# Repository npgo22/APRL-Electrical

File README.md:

# APRL KiCad Projects

APRL KiCad Projects.

## Setup
First, clone the repository with `git clone`. GitHub has a button which gives you the command to do this.
Then, you will have to use `git lfs pull` to get all the 3D models and images.

The projects here rely on `APRL_LIBS` and `KICAD_USER_TEMPLATE_DIR` being set. You can do this by:

1. Going to Preferences > Configure Paths...
2. Setting `APRL_LIBS` to wherever you cloned this repo + `/kicadlibs`.
3. Setting `KICAD_USER_TEMPLATE_DIR` to whatever you set in (2) + `/templates`

## New ALI (Current Project for FQ2026)

### Design
The exigence of this endeavour is twofold:
1. To test the analog frontend designs of our proposed boards for DPF
2. To replace the confusing and elaborate ALI electronics with something that is far better documented and easier to use

The ALI itself can continue to be used for years to come and this reworking of the electronics will not impact it at all. This is going to be its own separate electrical box altogether. The ALI has the following additional limitations, too:
1. Limited I/O
2. Bonded grounds between +24/12/5V power supplies
3. Unknown board-level design decisions/trade-offs made in off-the-shelf components leading to strange artifacts in various measurements
4. Is generally really difficult to understand
5. Mixes bodge-wired custom electronics, off-the-shelf parts, and protoboards
6. Generally has fairly poor mounting
7. Makes use of fairly terrible connectors which are partially damaged and/or have shields which are not properly tied to case GND
8. Is completely full, thus making it impossible to add more electronics
9. Has no methods of cooling, sans the empty hold in the side of the box which completely negate the weather rating of the box itself
10. Uses heterogenous embedded computing ecosystems, requiring cross-domain knowledge of embassy, STM32Cube, and Arduino while doing every single one of them somewhat wrong in one way or another
11. Lacks feedback in many places (error logging namely)
12. Is generally just really hard to work with

Therefore, we have started work on a true replacement. Each of the modules serve a specific task, and are hooked to a common ethernet-based network which is far more performant than the original layout while simultaneously being easier to understand and expand. If you want more I/O, you can just simply add another board within a few minutes. Likewise, by opting for cutouts in the enclosure over dedicated port holes, it is also far easier to revise significant parts of the design without needing to drill through steel. 

#### Power
This system is +5V and +24V only, with +3.3V regulated on each board.

### CANBUS vs Ethernet
On the ground station, we are planning to use Ethernet instead of CANBUS. While this means our session protocol will not be tested in a real-world hotfire scenario, it does mean we can fully exploit each of the features offered by ethernet:
- Higher bandwidth (upwards of ~50x) means we don't have to throttle anything including error logging
- Natural isolation means we don't need any special tricks to get grounded thermocouples to work
- Is just generally far more pleasant to work with
- Does not limit future design decisions should we decide to reuse anything

Each of the modules will have a CAN transceiver anyway available for testing.

## Repository layout

```
kicadlibs/                                 Shared KiCad libraries, referenced as ${APRL_LIBS}
  aprl/                                      APRL's custom symbols and footprints
  aprl/*-noct.pretty                         "aprl/" but without courtyards
  vendor/                                    Third-party libs
  kicad/                                     Vendored stock KiCad libraries
  models/                                    3D models
  APRL_*_Sheet.kicad_wks                     Drawing sheets
  jlcpcb-4layer.kicad_dru                    Canonical JLCPCB design rules
.github/scripts                              Helper scripts runnable via Just and GH actions

ali/v2/                                    New ALI electronics
ali/v1/                                    Old ALI electronics
ophio/                                     DPF Vehicle Boards
misc/                                      Other endeavours
```

## What's not in this repo
- Old code (incl thermocouple 1A's CubeMX and Embassy variants)
- Prototypes (pending ordering)
- ALI ADC hardware (pending import)

## AI Usage
You may use AI to research topics and to write one-off scripts which do minor modifications and automate tedious, minor tasks. For example, if you need to color in a bunch of models feel free to.

What you *cannot* use it for is end to end electrical design, layout, and documentation. Documents should be written by people, and a schematic falls under this category. Likewise, using AI to automate layout is A. ineffective because it does not generate high-quality layouts and B. defeats the purpose of this club, which is to learn about electronics.

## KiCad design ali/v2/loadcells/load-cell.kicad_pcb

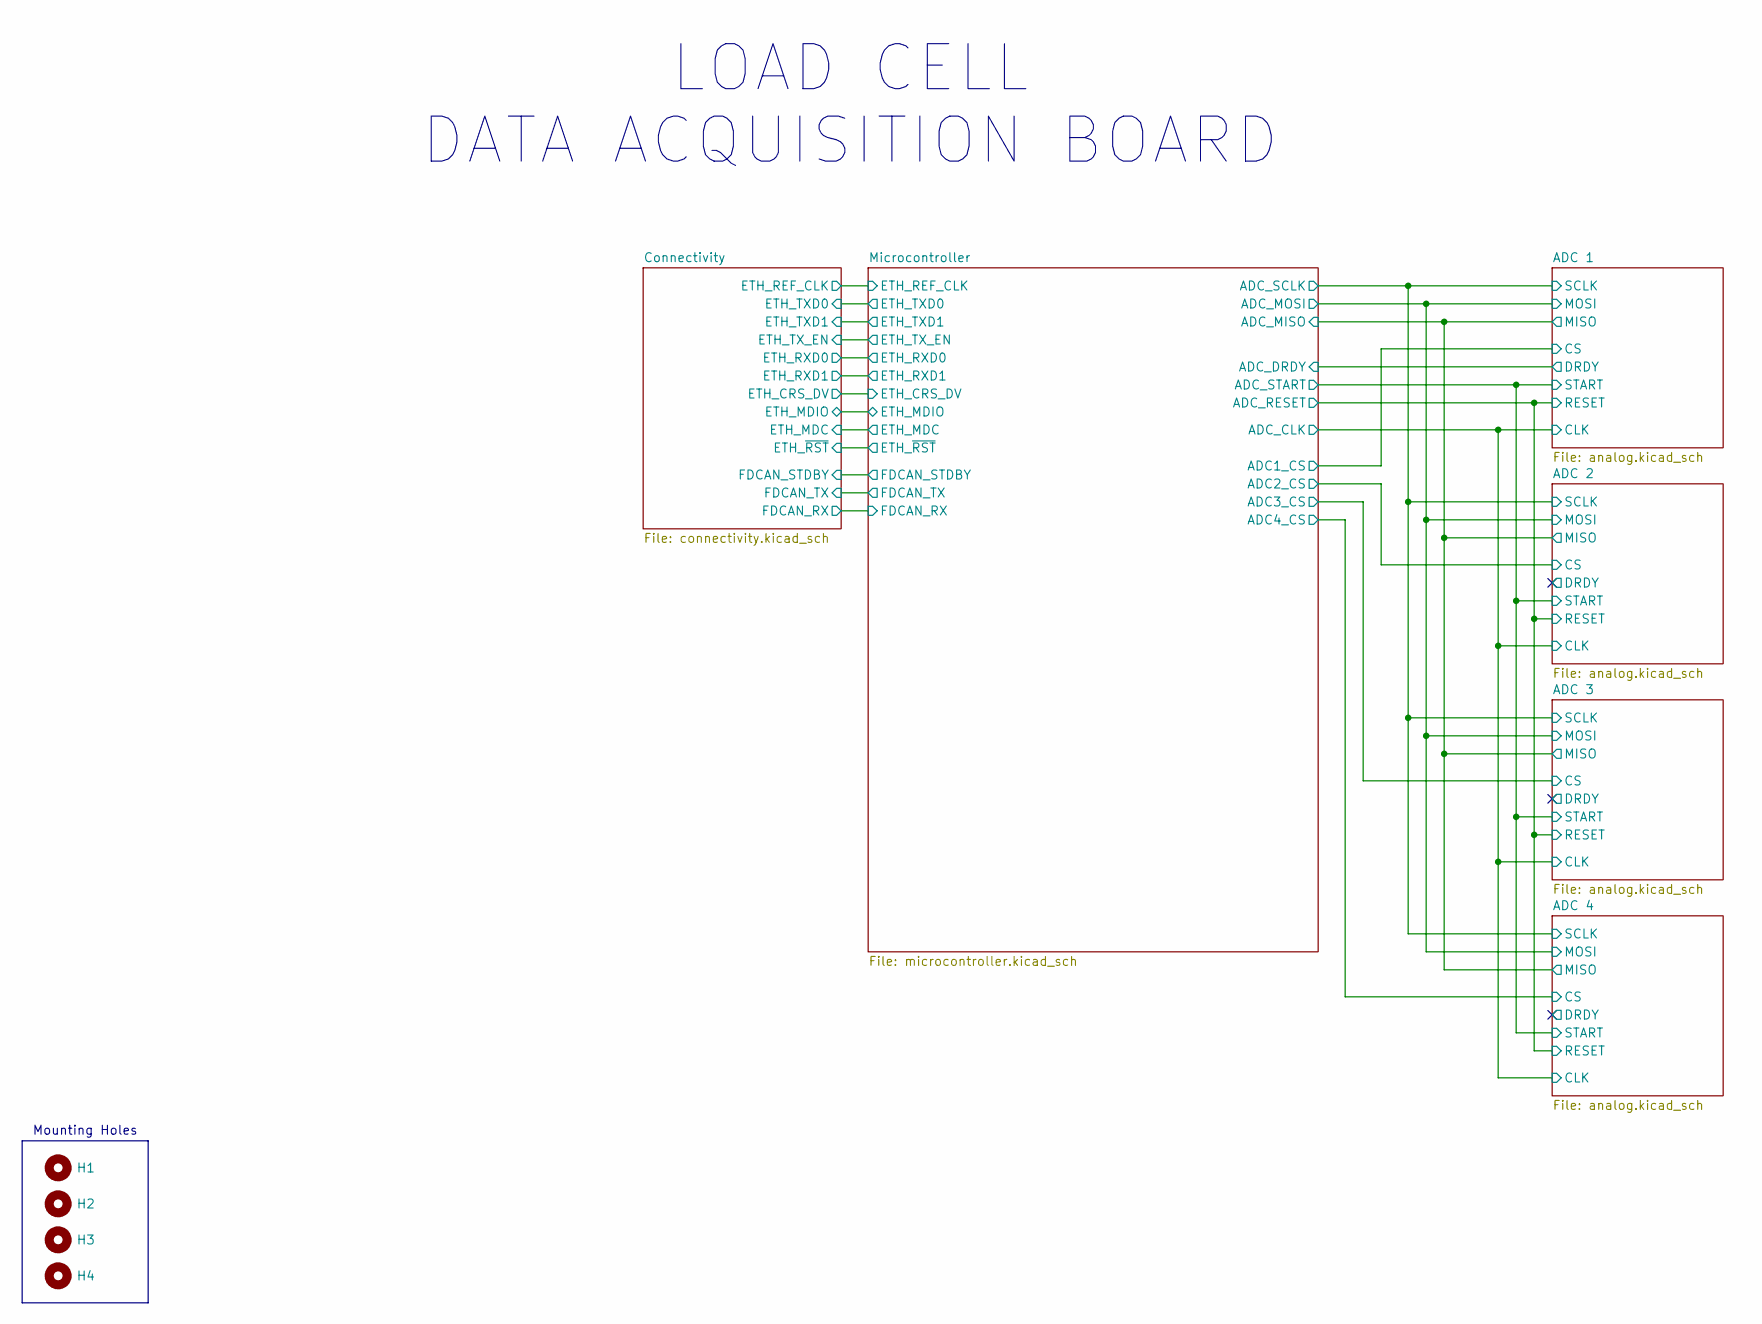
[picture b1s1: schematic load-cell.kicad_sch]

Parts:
H1, H2, H3, H4: MountingHole; MountingHole_3.2mm_M3

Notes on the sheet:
LOAD CELL DATA ACQUISITION BOARD
Mounting Holes

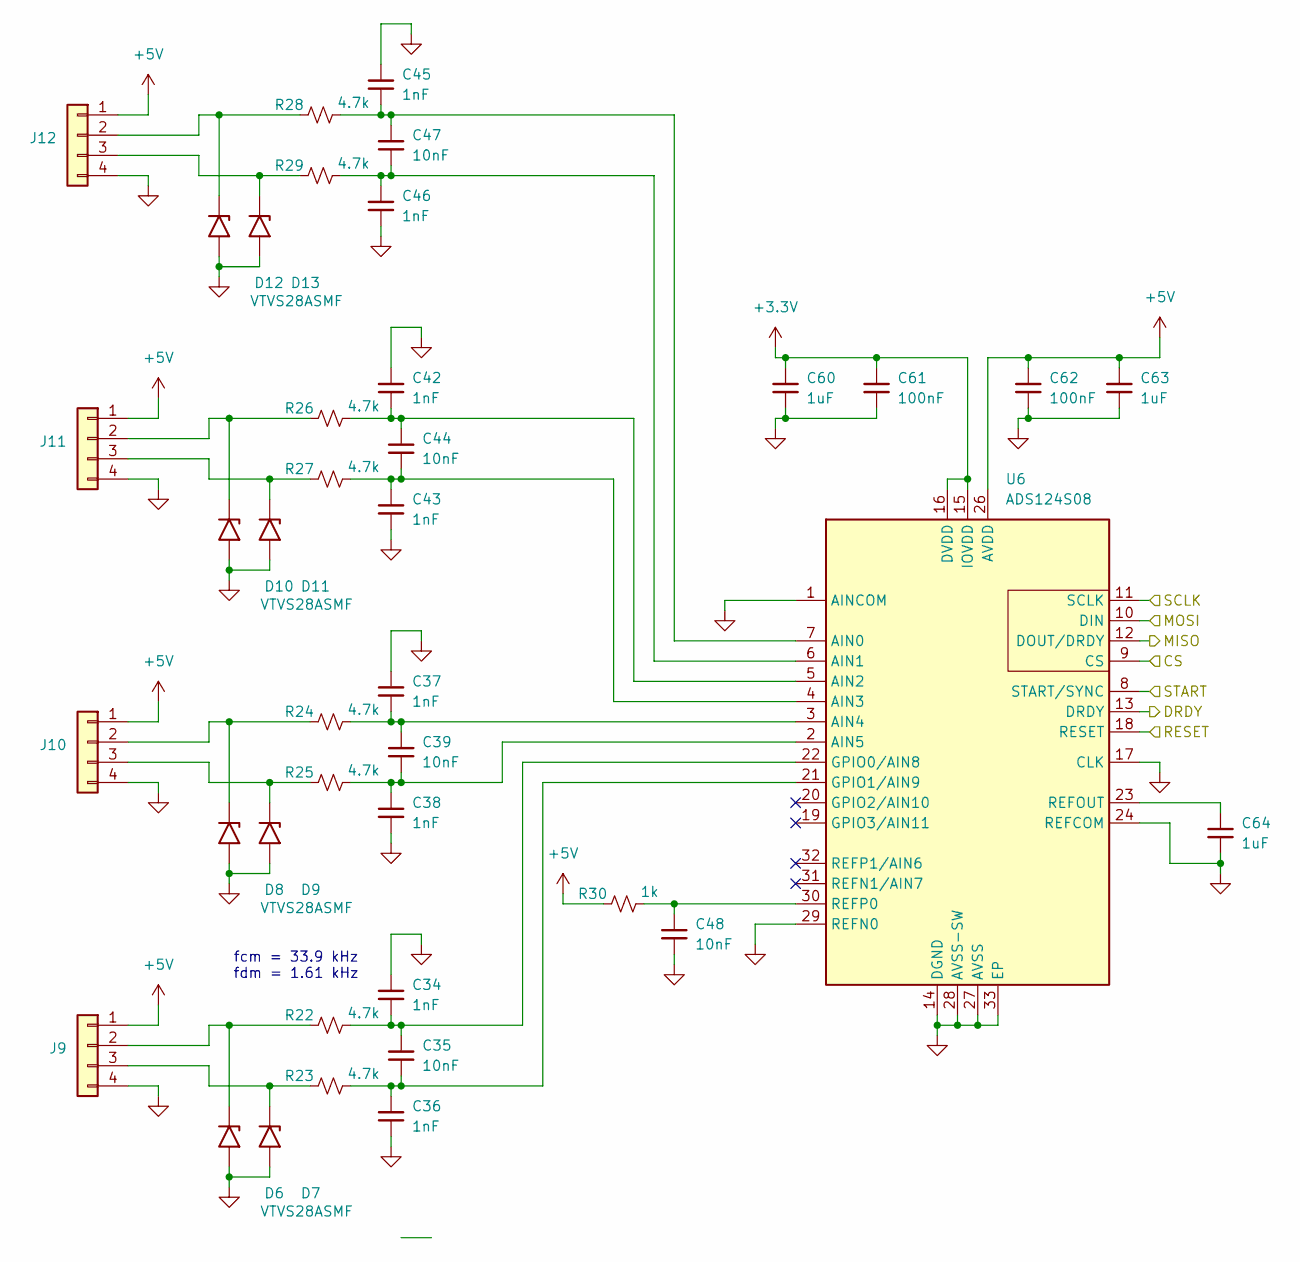
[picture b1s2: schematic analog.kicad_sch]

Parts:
C34, C36, C37, C38, C42, C43, C45, C46: 1nF; C_0603; MPN GRM1885C1H102FA01
C35, C39, C44, C47, C48: 10nF; C_0603; MPN GRM1885C1H103JA01
C60, C63, C64: 1uF; C_0603; MPN GRM188D72A105KE01
C61, C62: 100nF; C_0603; MPN GRM188R72A104KA35
D6, D7, D8, D9, D10, D11, D12, D13: VTVS28ASMF; D_SMF; MPN VTVS28ASMF-M3-08
J9, J10, J11, J12: Conn_01x04; Molex_CLIK-Mate_503159-0401_1x04-1MP_P1.50mm_Vertical; MPN 503159-0401
R22, R23, R24, R25, R26, R27, R28, R29: 4.7k; R_0603; MPN RT0603BRD074K7L
R30: 1k; R_0603; MPN RT0603BRD071KL
U6: ADS124S08; Texas_RHB0032M_VQFN-32-1EP_5x5mm_P0.5mm_EP2.1x2.1mm_Thermal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; MPN ADS124S08IRHBT

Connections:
+3.3V: C60.1, C61.1, U6.15 (IOVDD), U6.16 (DVDD); also elsewhere on the board
+5V: C62.1, C63.1, J9.1, J10.1, J11.1, J12.1, R30.1, U6.26 (AVDD); also elsewhere on the board
/ADC/CS: U6.9 (CS); also elsewhere on the board
/ADC/DRDY: U6.13 (DRDY); also elsewhere on the board
/ADC/MISO: U6.12 (DOUT/DRDY); also elsewhere on the board
/ADC/MOSI: U6.10 (DIN); also elsewhere on the board
/ADC/RESET: U6.18 (RESET); also elsewhere on the board
/ADC/SCLK: U6.11 (SCLK); also elsewhere on the board
/ADC/START: U6.8 (START/SYNC); also elsewhere on the board
GND: C34.2, C36.1, C37.2, C38.1, C42.2, C43.1, C45.2, C46.1, C48.1, C60.2, C61.2, C62.2, C63.2, C64.2, D6.2 (A2), D7.2 (A2), D8.2 (A2), D9.2 (A2), D10.2 (A2), D11.2 (A2), D12.2 (A2), D13.2 (A2), J9.4, J10.4, J11.4, J12.4, U6.1 (AINCOM), U6.14 (DGND), U6.17 (CLK), U6.24 (REFCOM), U6.27 (AVSS), U6.28 (AVSS-SW), U6.29 (REFN0), U6.33 (EP); also elsewhere on the board
unnamed: D6.1 (A1), J9.2, R22.1
unnamed: D7.1 (A1), J9.3, R23.1
unnamed: D8.1 (A1), J10.2, R24.1
unnamed: D9.1 (A1), J10.3, R25.1
unnamed: D10.1 (A1), J11.2, R26.1
unnamed: D11.1 (A1), J11.3, R27.1
unnamed: D12.1 (A1), J12.2, R28.1
unnamed: D13.1 (A1), J12.3, R29.1
unnamed: C45.1, C47.2, R28.2, U6.7 (AIN0)
unnamed: C46.2, C47.1, R29.2, U6.6 (AIN1)
unnamed: C42.1, C44.2, R26.2, U6.5 (AIN2)
unnamed: C43.2, C44.1, R27.2, U6.4 (AIN3)
unnamed: C37.1, C39.2, R24.2, U6.3 (AIN4)
unnamed: C38.2, C39.1, R25.2, U6.2 (AIN5)
unnamed: C34.1, C35.2, R22.2, U6.22 (GPIO0/AIN8)
unnamed: C35.1, C36.2, R23.2, U6.21 (GPIO1/AIN9)
unnamed: C64.1, U6.23 (REFOUT)
unnamed: C48.2, R30.2, U6.30 (REFP0)

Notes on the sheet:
fcm = 33.9 kHz fdm = 1.61 kHz

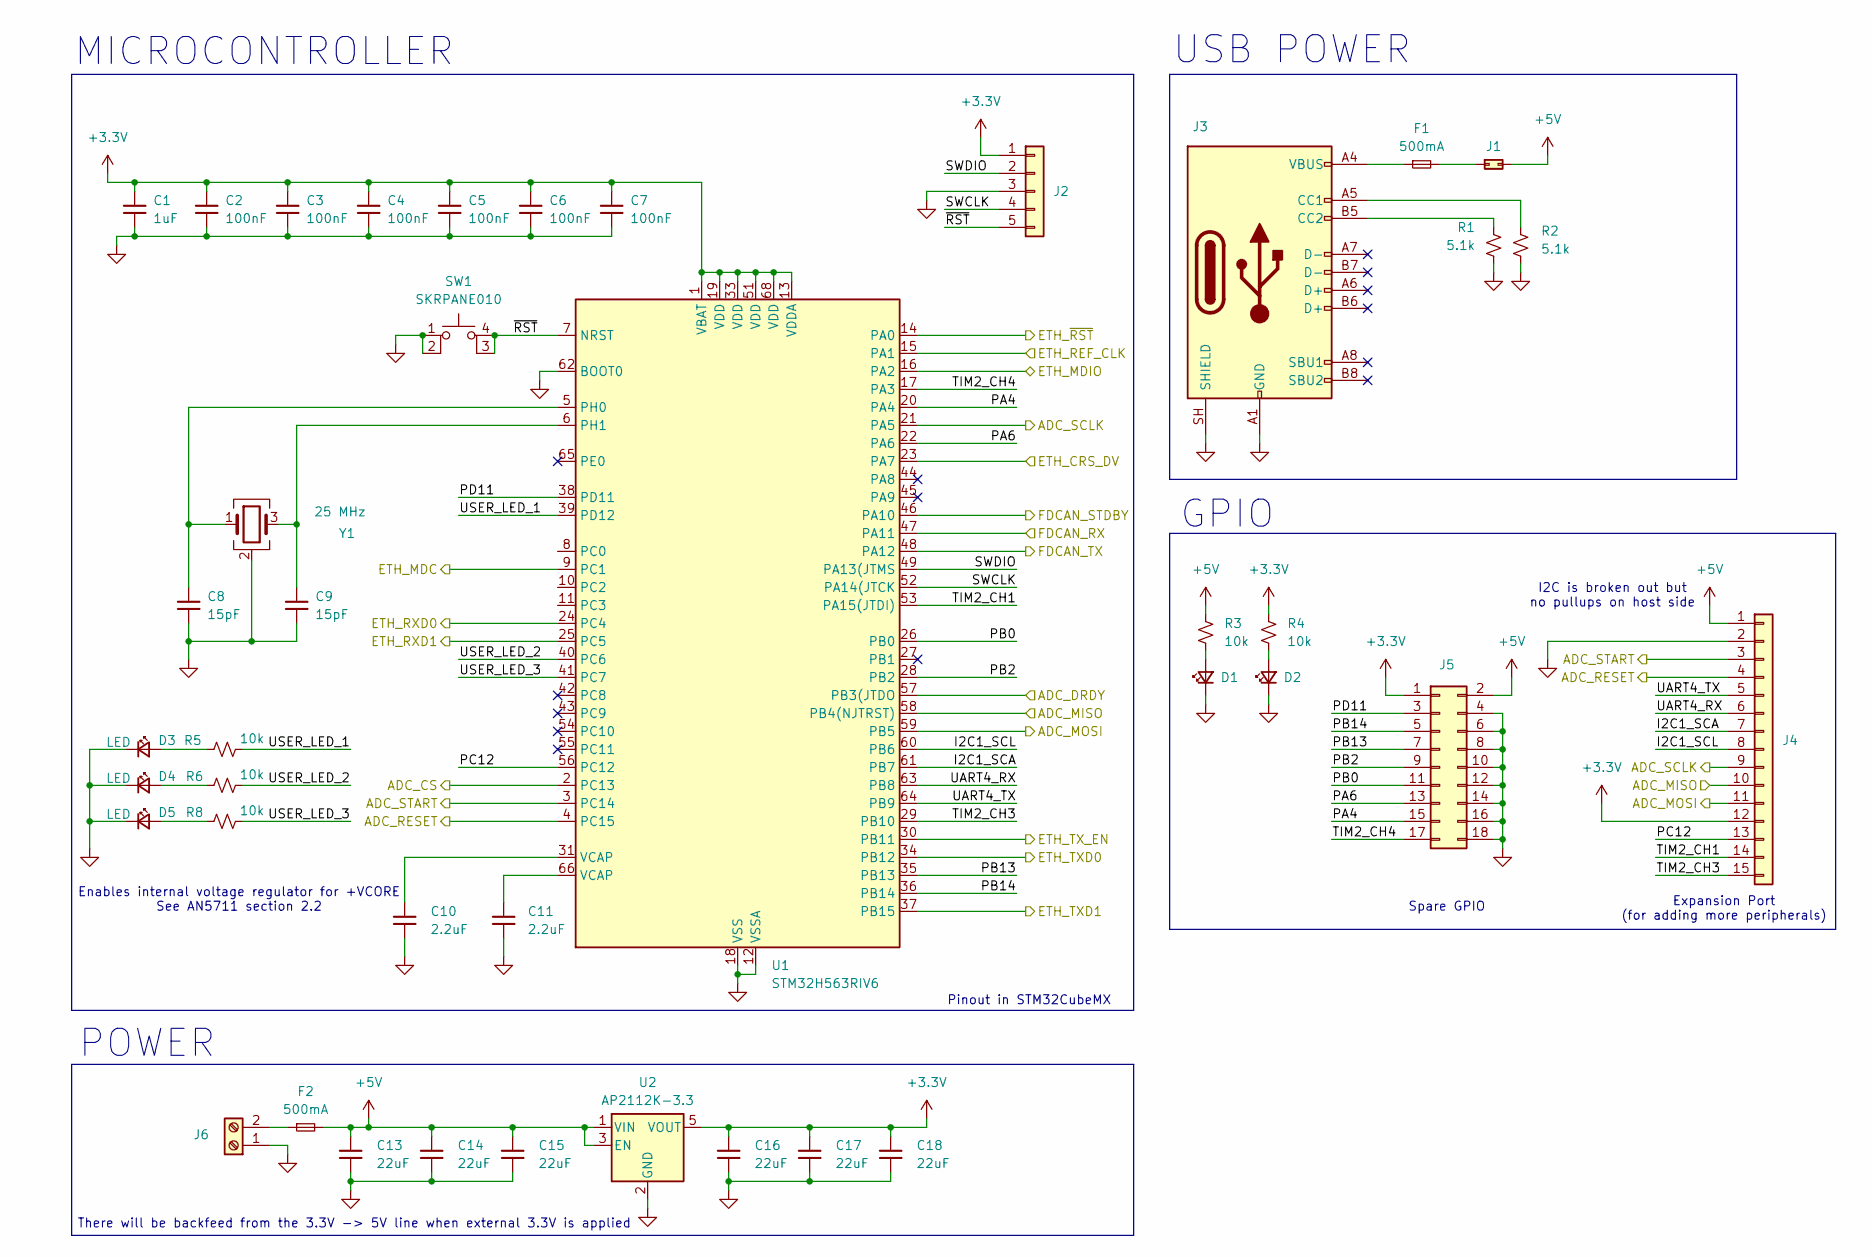
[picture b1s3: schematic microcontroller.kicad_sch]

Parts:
C1: 1uF; C_0603; MPN GRM188D72A105KE01
C2, C3, C4, C5, C6, C7: 100nF; C_0603; MPN GRM188R72A104KA35
C8, C9: 15pF; C_0603; MPN GRM1885C2E150FW07
C10, C11: 2.2uF; C_0603; MPN GRM188R71A225KE15
C13, C14, C15, C16, C17, C18: 22uF; C_0805; MPN GRM21BZ71A226ME15
D1, D2, D3, D4, D5: LED; LED_0603
F1, F2: 500mA; Fuse_0805_2012Metric; MPN 0805L050WR
J1: Conn_02x01; PinHeader_1x02_P2.54mm_Vertical
J2: Conn_01x05; Molex_CLIK-Mate_503159-0501_1x05-1MP_P1.50mm_Vertical; MPN 503159-0501
J3: USB_C_Receptacle_USB2.0_16P; USB_C_Receptacle_G-Switch_GT-USB-7051x; MPN GT-USB-7051A
J4: Conn_01x15; Molex_CLIK-Mate_503159-1501_1x15-1MP_P1.50mm_Vertical; MPN 503159-1501
J5: Conn_02x09_Counter_Clockwise; IDC-Header_2x09_P2.54mm_Vertical
J6: Screw_Terminal_01x02; PhoenixContact_MSTBV_2,5_2-GF-5,08_1x02_P5.08mm_Vertical_Th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; MPN MSTBV 2,5/ 2-GF-5,08
R1, R2: 5.1k; R_0603; MPN RC0603FR-075K1L
R3, R4, R5, R6, R8: 10k; R_0603; MPN RC0603FR-0710KL
SW1: SKRPANE010; MPN SKRPANE010
U1: STM32H563RIV6; QFN-68-1EP_8x8mm_P0.4mm_EP6.4x6.4mm; MPN STM32H563RIV6
U2: AP2112K-3.3; SOT-23-5; MPN AP2112K-3.3TRG1
Y1: 25 MHz; 3225-4P-L; MPN X1E0000210139

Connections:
+3.3V: C1.1, C2.1, C3.1, C4.1, C5.1, C6.1, C7.1, C16.1, C17.1, C18.1, J2.1, J4.12, J5.1, R4.1, U1.1 (VBAT), U1.13 (VDDA), U1.19 (VDD), U1.33 (VDD), U1.51 (VDD), U1.68 (VDD), U2.5 (VOUT); also elsewhere on the board
+5V: C13.1, C14.1, C15.1, F2.2, J1.2, J4.1, J5.2, R3.1, U2.1 (VIN), U2.3 (EN); also elsewhere on the board
/ADC/CS: U1.2 (PC13); also elsewhere on the board
/ADC/DRDY: U1.57 (PB3(JTDO); also elsewhere on the board
/ADC/MISO: J4.10, U1.58 (PB4(NJTRST)); also elsewhere on the board
/ADC/MOSI: J4.11, U1.59 (PB5); also elsewhere on the board
/ADC/RESET: J4.4, U1.4 (PC15); also elsewhere on the board
/ADC/SCLK: J4.9, U1.21 (PA5); also elsewhere on the board
/ADC/START: J4.3, U1.3 (PC14); also elsewhere on the board
/Connectivity/ETH_CRS_DV: U1.23 (PA7); also elsewhere on the board
/Connectivity/ETH_MDC: U1.9 (PC1); also elsewhere on the board
/Connectivity/ETH_MDIO: U1.16 (PA2); also elsewhere on the board
/Connectivity/ETH_REF_CLK: U1.15 (PA1); also elsewhere on the board
/Connectivity/ETH_RXD0: U1.24 (PC4); also elsewhere on the board
/Connectivity/ETH_RXD1: U1.25 (PC5); also elsewhere on the board
/Connectivity/ETH_TXD0: U1.34 (PB12); also elsewhere on the board
/Connectivity/ETH_TXD1: U1.37 (PB15); also elsewhere on the board
/Connectivity/ETH_TX_EN: U1.30 (PB11); also elsewhere on the board
/Connectivity/ETH_~RST: U1.14 (PA0); also elsewhere on the board
/Connectivity/FDCAN_RX: U1.47 (PA11); also elsewhere on the board
/Connectivity/FDCAN_STDBY: U1.46 (PA10); also elsewhere on the board
/Connectivity/FDCAN_TX: U1.48 (PA12); also elsewhere on the board
/Microcontroller/I2C1_SCA: J4.7, U1.61 (PB7)
/Microcontroller/I2C1_SCL: J4.8, U1.60 (PB6)
/Microcontroller/PA4: J5.15, U1.20 (PA4)
/Microcontroller/PA6: J5.13, U1.22 (PA6)
/Microcontroller/PB0: J5.11, U1.26 (PB0)
/Microcontroller/PB2: J5.9, U1.28 (PB2)
/Microcontroller/PB13: J5.7, U1.35 (PB13)
/Microcontroller/PB14: J5.5, U1.36 (PB14)
/Microcontroller/PC12: J4.13, U1.56 (PC12)
/Microcontroller/PD11: J5.3, U1.38 (PD11)
/Microcontroller/SWCLK: J2.4, U1.52 (PA14(JTCK)
/Microcontroller/SWDIO: J2.2, U1.49 (PA13(JTMS)
/Microcontroller/TIM2_CH1: J4.14, U1.53 (PA15(JTDI))
/Microcontroller/TIM2_CH3: J4.15, U1.29 (PB10)
/Microcontroller/TIM2_CH4: J5.17, U1.17 (PA3)
/Microcontroller/UART4_RX: J4.6, U1.63 (PB8)
/Microcontroller/UART4_TX: J4.5, U1.64 (PB9)
/Microcontroller/USER_LED_1: R5.2, U1.39 (PD12)
/Microcontroller/USER_LED_2: R6.2, U1.40 (PC6)
/Microcontroller/USER_LED_3: R8.2, U1.41 (PC7)
/Microcontroller/~RST: J2.5, SW1.3 (K), SW1.4 (A), U1.7 (NRST)
GND: C1.2, C2.2, C3.2, C4.2, C5.2, C6.2, C7.2, C8.2, C9.2, C10.2, C11.2, C13.2, C14.2, C15.2, C16.2, C17.2, C18.2, D1.1 (K), D2.1 (K), D3.1 (K), D4.1 (K), D5.1 (K), J2.3, J3.A1 (GND), J3.A12 (GND), J3.B1 (GND), J3.B12 (GND), J3.SH (SHIELD), J4.2, J5.4, J5.6, J5.8, J5.10, J5.12, J5.14, J5.16, J5.18, J6.1, R1.1, R2.2, SW1.1, SW1.2, U1.12 (VSSA), U1.18 (VSS), U1.32 (VSS), U1.50 (VSS), U1.62 (BOOT0), U1.67 (VSS), U1.69 (VSS), U2.2 (GND), Y1.2 (G), Y1.4 (G); also elsewhere on the board
unnamed: C10.1, U1.31 (VCAP)
unnamed: C11.1, U1.66 (VCAP)
unnamed: D1.2 (A), R3.2
unnamed: D2.2 (A), R4.2
unnamed: D3.2 (A), R5.1
unnamed: D4.2 (A), R6.1
unnamed: D5.2 (A), R8.1
unnamed: F1.1, J3.A4 (VBUS), J3.A9 (VBUS), J3.B4 (VBUS), J3.B9 (VBUS)
unnamed: F1.2, J1.1
unnamed: J3.A5 (CC1), R2.1
unnamed: J3.B5 (CC2), R1.2
unnamed: F2.1, J6.2
unnamed: C8.1, U1.5 (PH0), Y1.1
unnamed: C9.1, U1.6 (PH1), Y1.3

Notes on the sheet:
Enables internal voltage regulator for +VCORE See AN5711 section 2.2
MICROCONTROLLER
There will be backfeed from the 3.3V -> 5V line when external 3.3V is applied
USB POWER
Spare GPIO
POWER
Expansion Port (for adding more peripherals)
Pinout in STM32CubeMX
I2C is broken out but no pullups on host side
GPIO

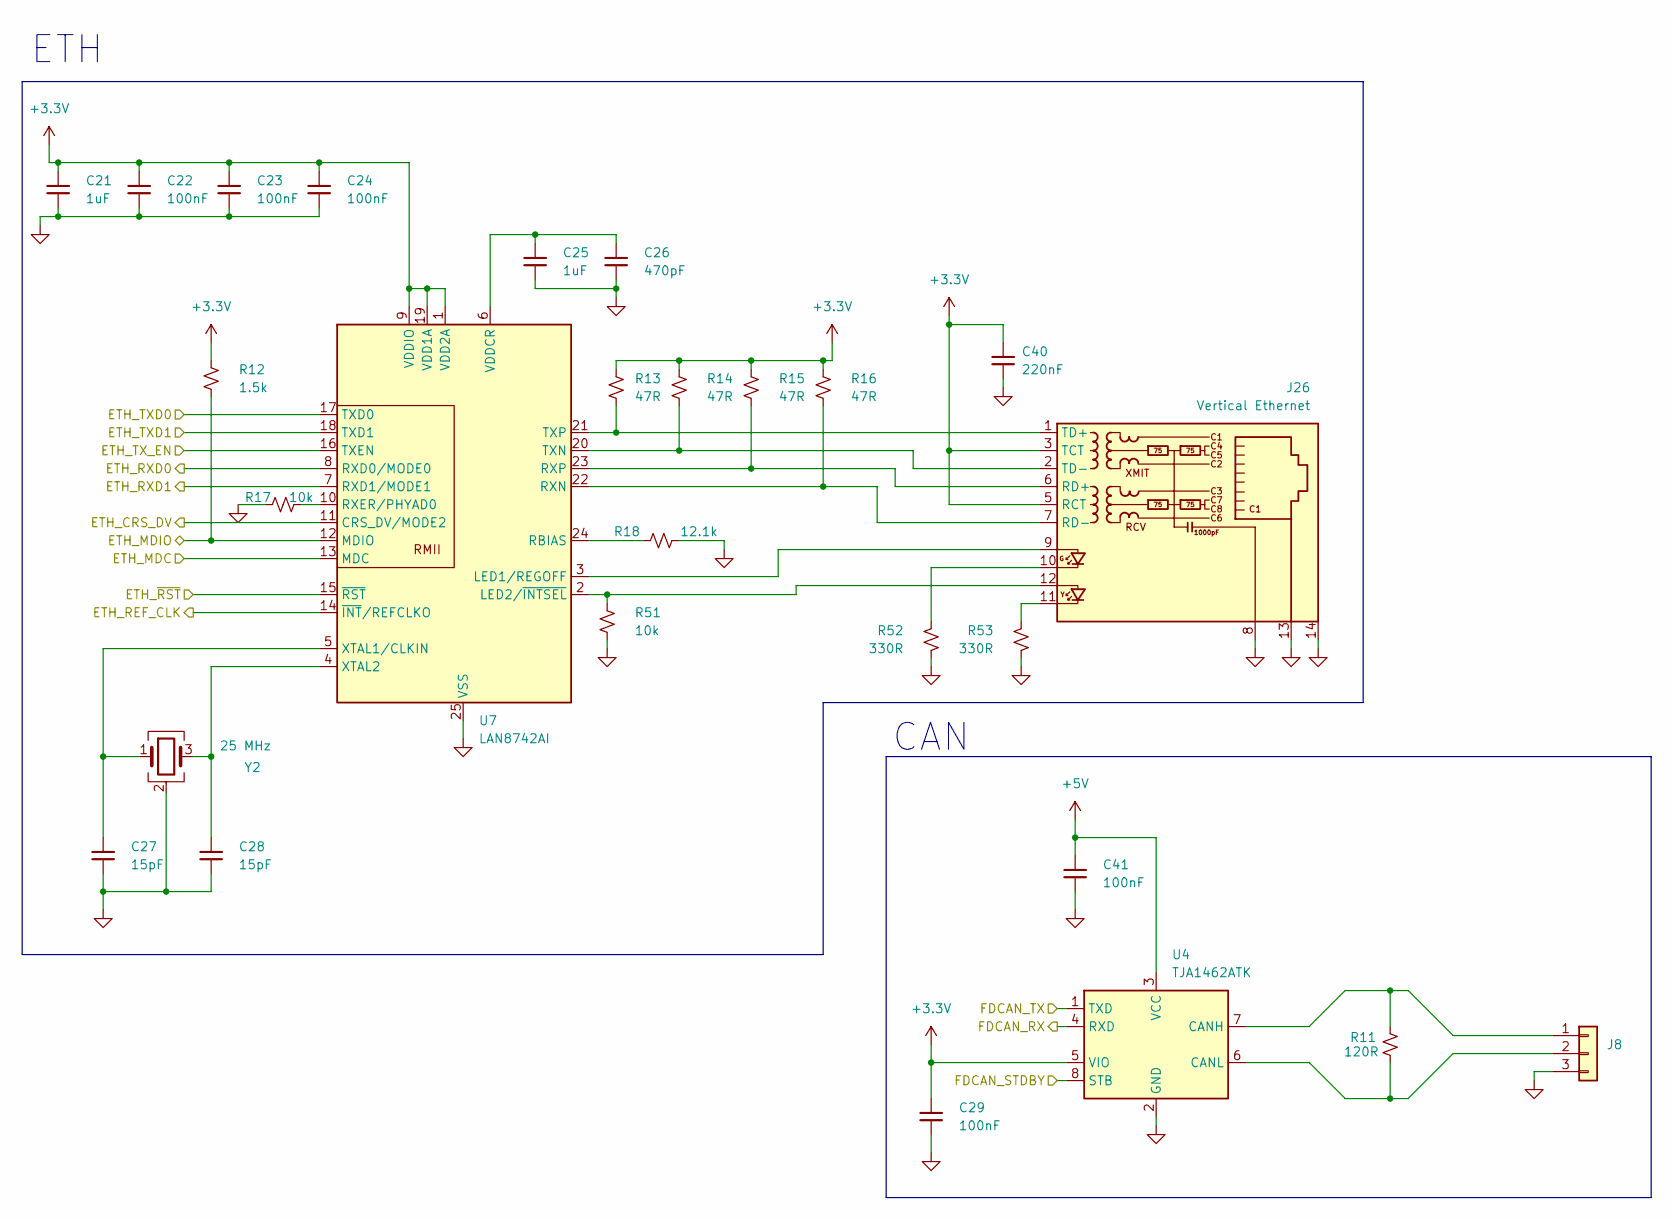
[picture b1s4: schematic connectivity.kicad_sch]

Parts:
C21, C25: 1uF; C_0603; MPN GRM188D72A105KE01
C22, C23, C24, C29, C41: 100nF; C_0603; MPN GRM188R72A104KA35
C26: 470pF; C_0603; MPN GRM1885C1H471JA01
C27, C28: 15pF; C_0603; MPN GRM1885C2E150FW07
C40: 220nF; C_0603; MPN GRM188R71H224KAC4
J8: Conn_01x03; Molex_CLIK-Mate_503159-0301_1x03-1MP_P1.50mm_Vertical; MPN 503159-0301
J26: Vertical Ethernet; RJ45_Hanrun_HY951180A_Vertical; MPN HY951180A
R11: 120R; R_0603; MPN AC0603FR-07120RL
R12: 1.5k; R_0603; MPN RC0603FR-071K5L
R13, R14, R15, R16: 47R; R_0603; MPN RC0603FR-0747RL
R17, R51: 10k; R_0603; MPN RC0603FR-0710KL
R18: 12.1k; R_0603; MPN RT0603BRD0712K1L
R52, R53: 330R; R_0603; MPN RC0603FR-07330RL
U4: TJA1462ATK; HVSON-8-1EP_3x3mm_P0.65mm_EP1.6x2.4mm_ThermalVias; MPN TJA1462ATK/0Z
U7: LAN8742AI; VQFN-24-1EP_4x4mm_P0.5mm_EP2.5x2.5mm_ThermalVias; MPN LAN8742AI-CZ-TR
Y2: 25 MHz; 3225-4P-L; MPN X1E0000210139

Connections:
+3.3V: C21.1, C22.1, C23.1, C24.1, C29.1, C40.1, J26.3 (TCT), J26.5 (RCT), R12.1, R13.1, R14.1, R15.1, R16.1, U4.5 (VIO), U7.1 (VDD2A), U7.9 (VDDIO), U7.19 (VDD1A); also elsewhere on the board
+5V: C41.1, U4.3 (VCC); also elsewhere on the board
/Connectivity/ETH_CRS_DV: U7.11 (CRS_DV/MODE2); also elsewhere on the board
/Connectivity/ETH_MDC: U7.13 (MDC); also elsewhere on the board
/Connectivity/ETH_MDIO: R12.2, U7.12 (MDIO); also elsewhere on the board
/Connectivity/ETH_REF_CLK: U7.14 (~INT/REFCLKO); also elsewhere on the board
/Connectivity/ETH_RXD0: U7.8 (RXD0/MODE0); also elsewhere on the board
/Connectivity/ETH_RXD1: U7.7 (RXD1/MODE1); also elsewhere on the board
/Connectivity/ETH_TXD0: U7.17 (TXD0); also elsewhere on the board
/Connectivity/ETH_TXD1: U7.18 (TXD1); also elsewhere on the board
/Connectivity/ETH_TX_EN: U7.16 (TXEN); also elsewhere on the board
/Connectivity/ETH_~RST: U7.15 (~RST); also elsewhere on the board
/Connectivity/FDCAN_RX: U4.4 (RXD); also elsewhere on the board
/Connectivity/FDCAN_STDBY: U4.8 (STB); also elsewhere on the board
/Connectivity/FDCAN_TX: U4.1 (TXD); also elsewhere on the board
GND: C21.2, C22.2, C23.2, C24.2, C25.2, C26.2, C27.2, C28.2, C29.2, C40.2, C41.2, J8.3, J26.8, J26.13, J26.14, R17.1, R18.2, R51.2, R52.2, R53.2, U4.2 (GND), U4.9 (GND), U7.25 (VSS), Y2.2 (G), Y2.4 (G); also elsewhere on the board
unnamed: J8.1, R11.2, U4.7 (CANH)
unnamed: J8.2, R11.1, U4.6 (CANL)
unnamed: J26.10, R52.1
unnamed: J26.11, R53.1
unnamed: J26.6 (RD+), R15.2, U7.23 (RXP)
unnamed: J26.7 (RD-), R16.2, U7.22 (RXN)
unnamed: J26.1 (TD+), R13.2, U7.21 (TXP)
unnamed: J26.2 (TD-), R14.2, U7.20 (TXN)
unnamed: J26.9, U7.3 (LED1/REGOFF)
unnamed: J26.12, R51.1, U7.2 (LED2/~INTSEL)
unnamed: R18.1, U7.24 (RBIAS)
unnamed: R17.2, U7.10 (RXER/PHYAD0)
unnamed: C25.1, C26.1, U7.6 (VDDCR)
unnamed: C27.1, U7.5 (XTAL1/CLKIN), Y2.1
unnamed: C28.1, U7.4 (XTAL2), Y2.3

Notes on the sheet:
ETH
CAN

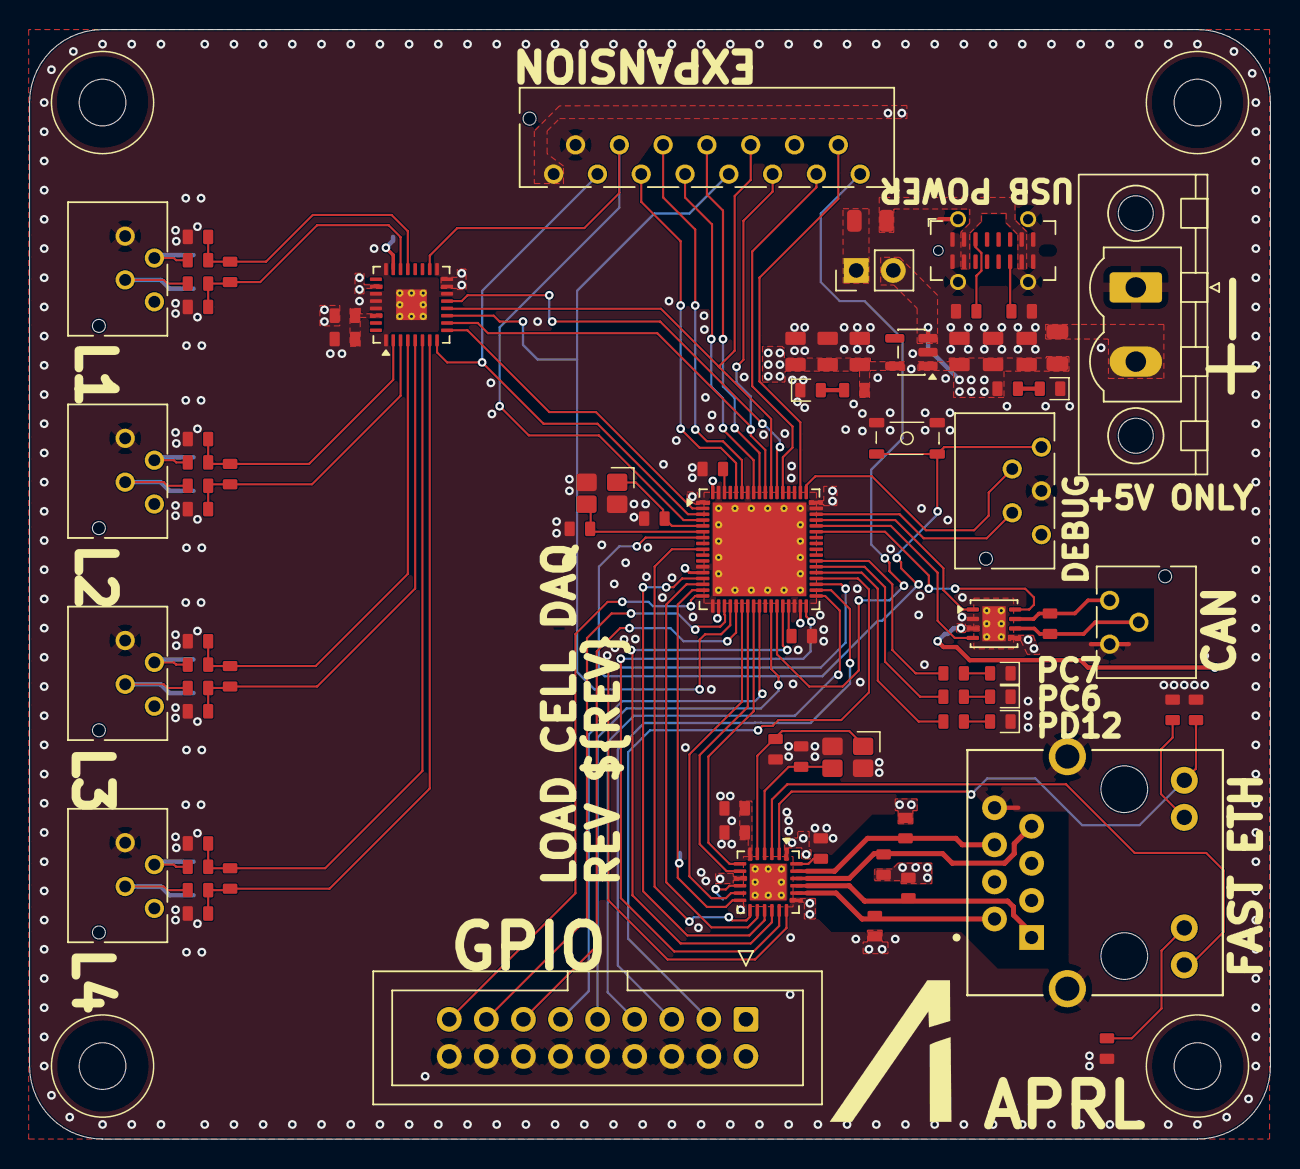
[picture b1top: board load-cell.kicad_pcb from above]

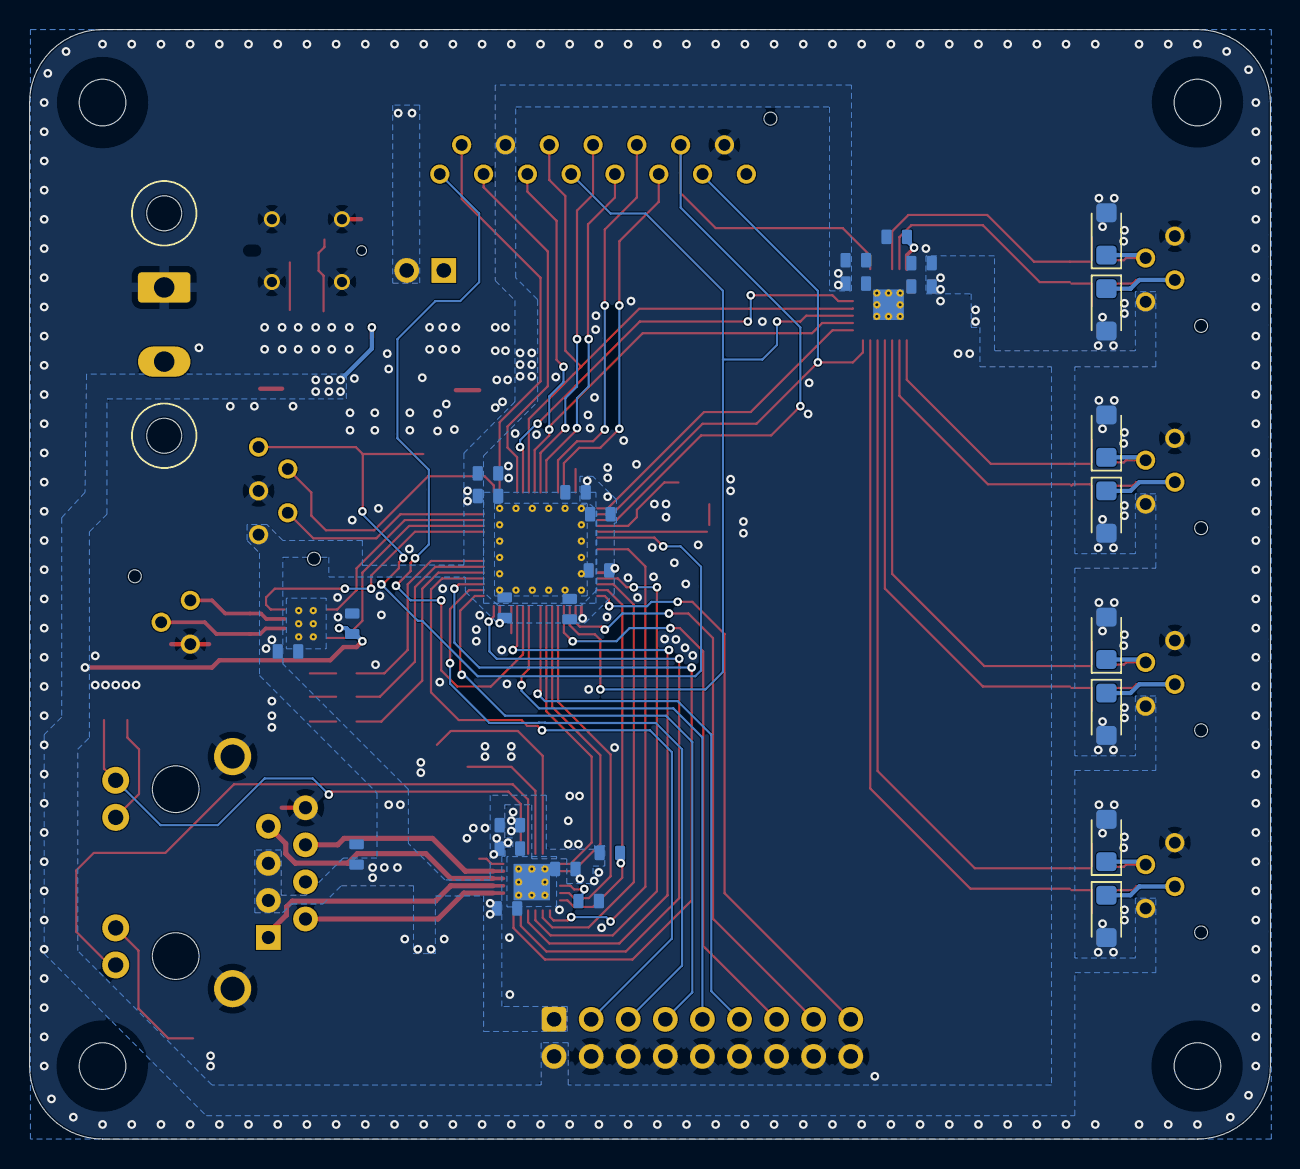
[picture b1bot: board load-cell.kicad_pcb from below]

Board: 4 copper layers, 85.0 x 76.0 mm, 112 parts (29 on the bottom side), 91 nets.

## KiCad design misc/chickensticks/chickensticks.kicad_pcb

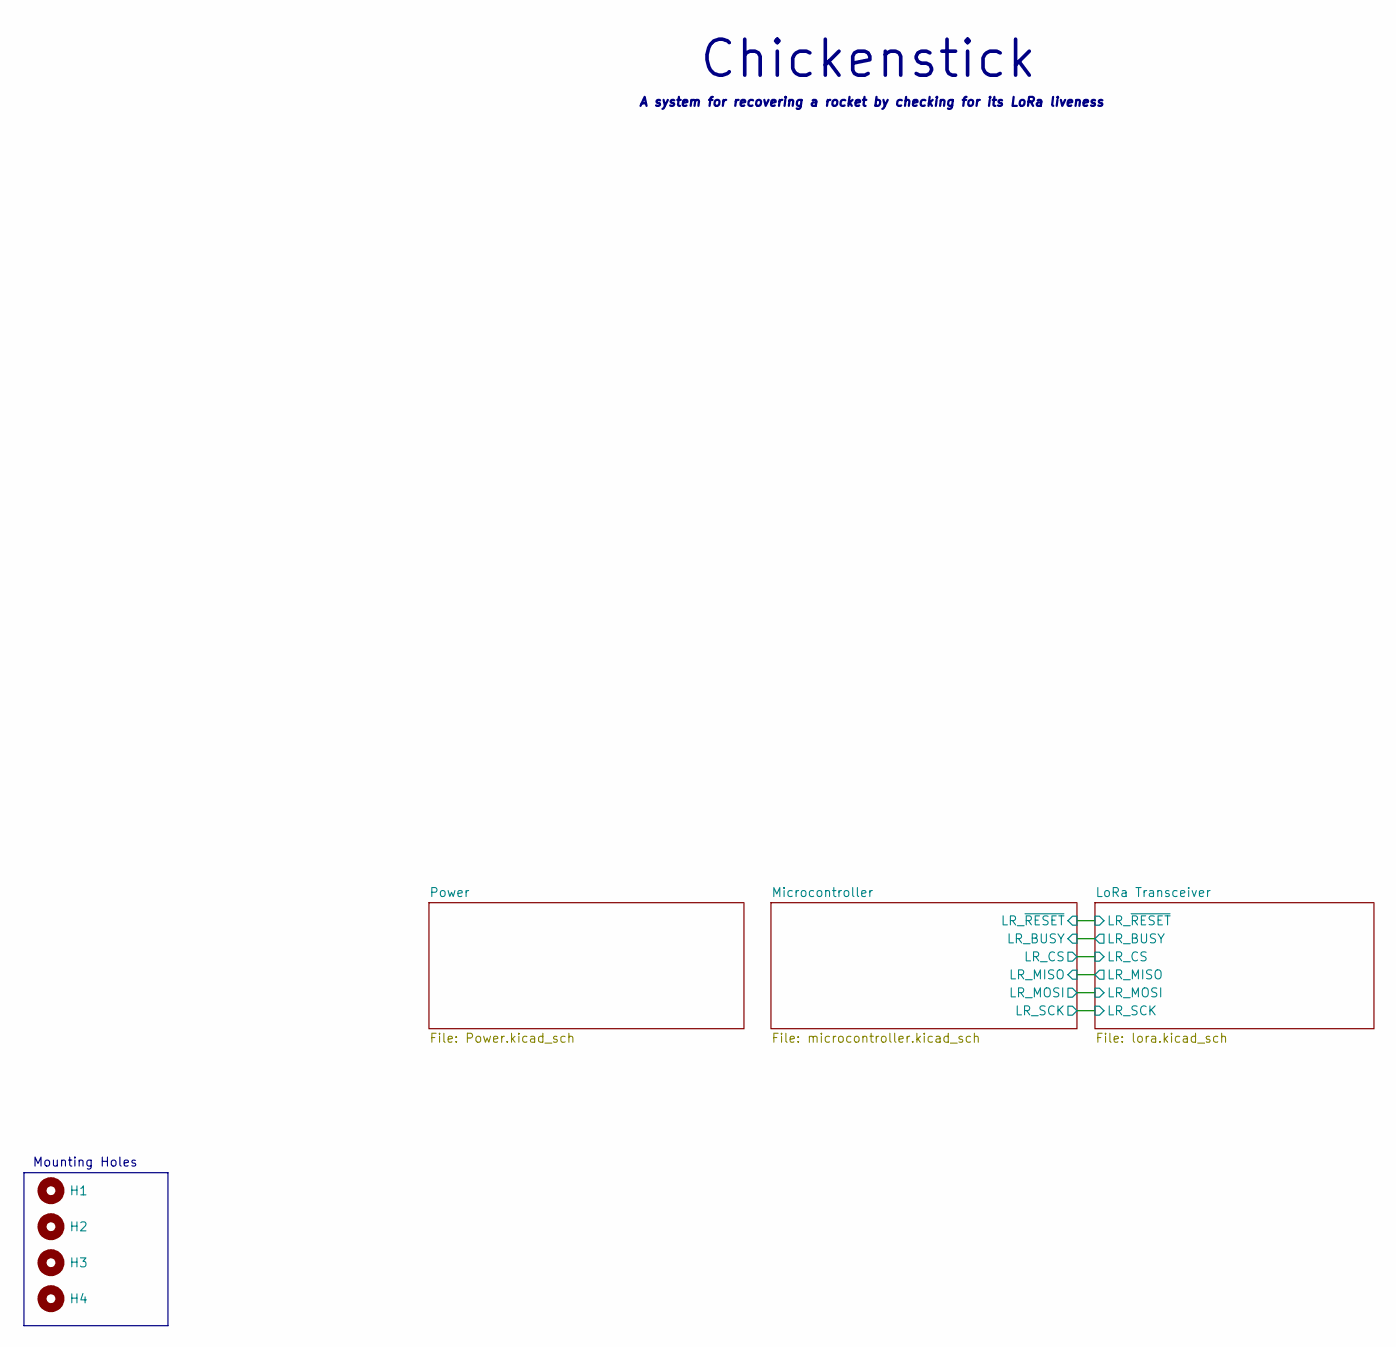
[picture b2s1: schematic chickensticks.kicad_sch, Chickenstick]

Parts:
H1, H2, H3, H4: MountingHole; MountingHole_3.2mm_M3

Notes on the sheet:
Chickenstick
A system for recovering a rocket by checking for its LoRa liveness
Mounting Holes
